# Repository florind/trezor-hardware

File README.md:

# Hardware design of Trezor

##
Using only 0603 components instead of 0402. Beware, the pushbuttons are also changed with https://www.mouser.de/ProductDetail/506-147873-2 (I have those).

https://trezor.io/

## Open Source Hardware

The content of this repo is dual licensed under the following licenses:
* [GNU Affero General Public License v3](COPYING)
* [CERN Open Hardware Licence Version 2 - Strongly Reciprocal](LICENSE)

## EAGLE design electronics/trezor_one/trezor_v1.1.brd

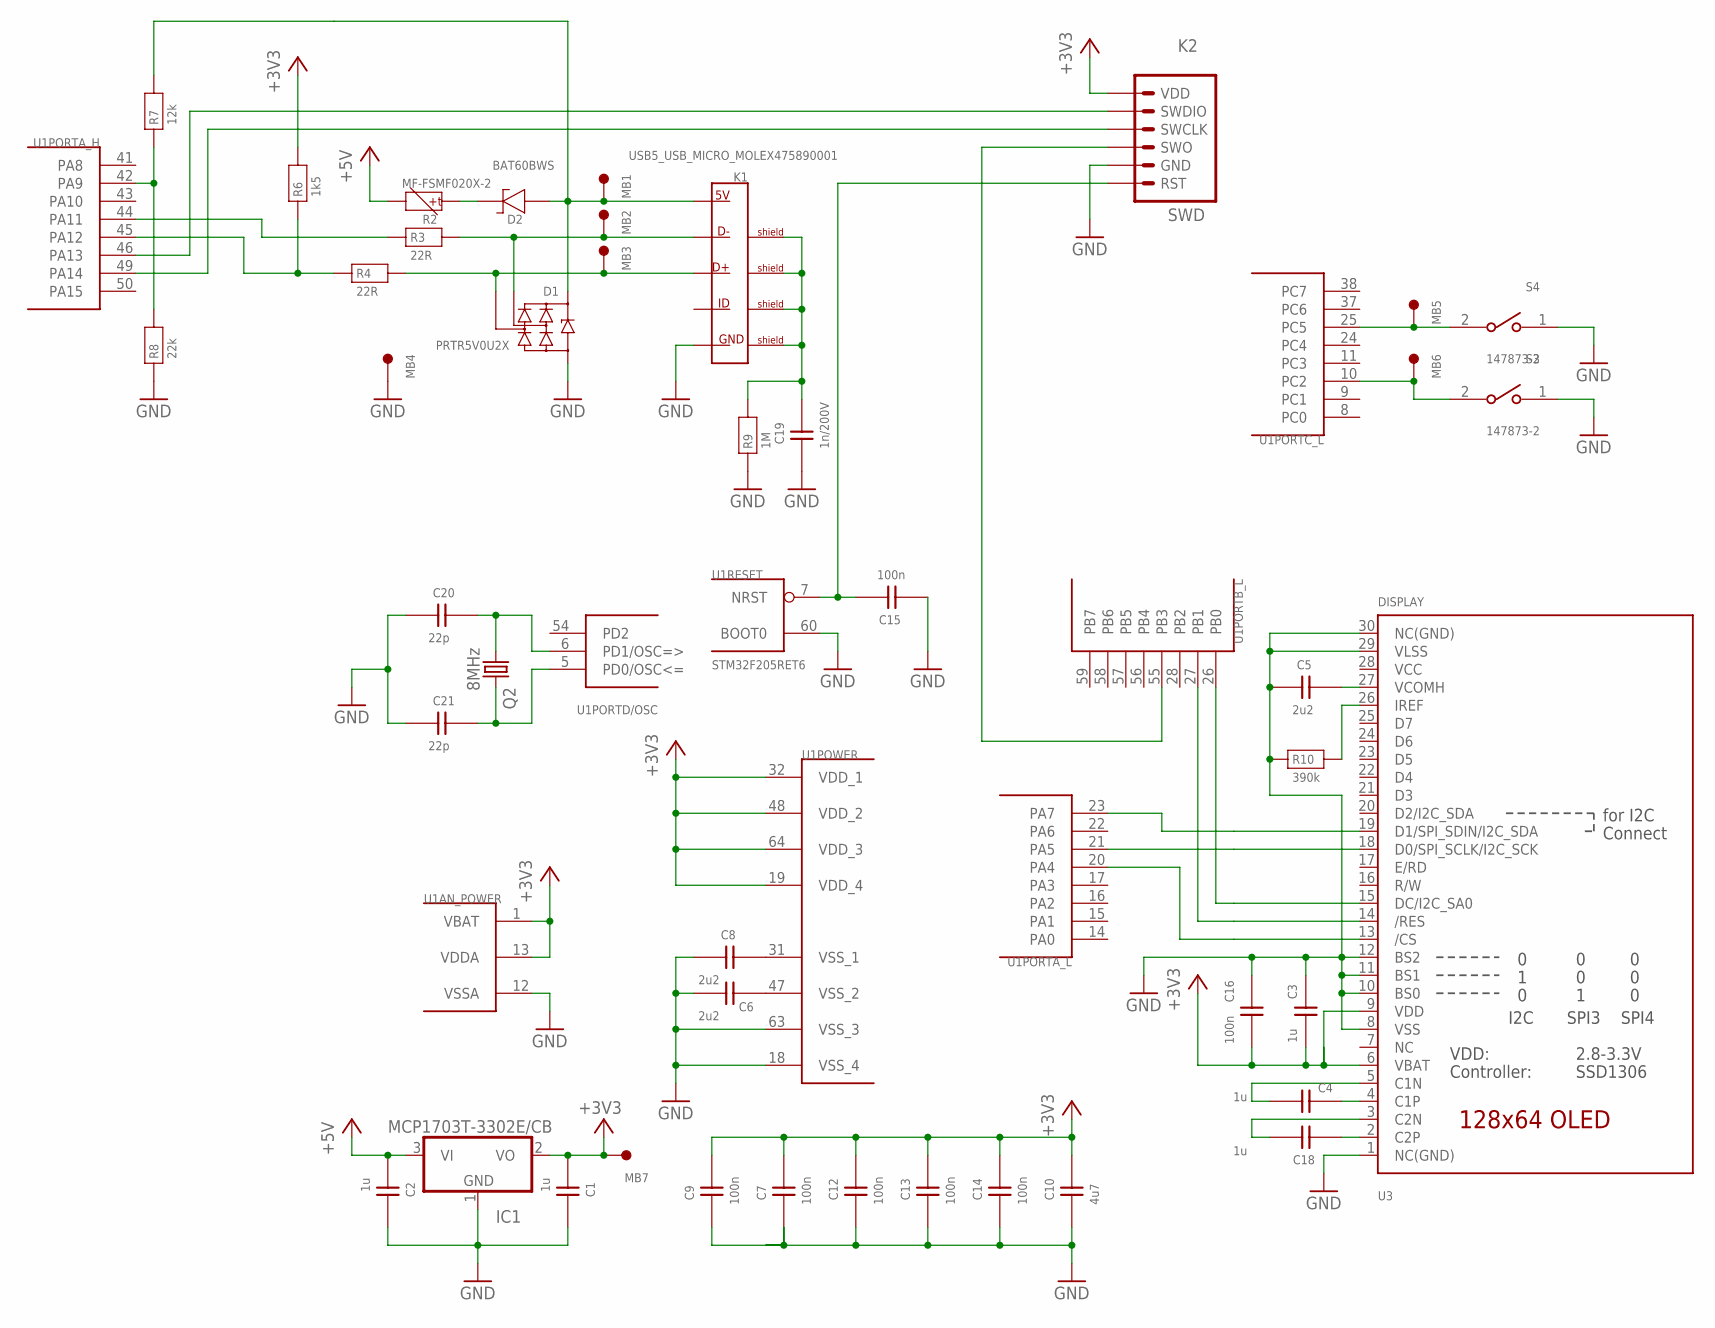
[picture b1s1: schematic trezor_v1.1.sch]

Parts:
C1, C2, C3, C4, C18: 1u; 0603
C5, C6, C8: 2u2; 0603
C7, C9, C12, C13, C14, C15, C16: 100n; 0603
C10: 4u7; 0603
C19: 1n/200V; 0603
C20, C21: 22p; 0603
D1: PRTR5V0U2X; SOT143B
D2: BAT60BWS; SOD323
IC1: MCP1703T-3302E/CB; SOT23
K1: USB5_USB_MICRO_MOLEX475890001; USB_MICRO-MOLEX475890001
K2: SWD
MB1, MB2, MB3, MB4, MB5, MB6, MB7: MB_1.50; MB1.5
Q2: 8MHz; CTS406
R2: MF-FSMF020X-2; 0603
R3, R4: 22R; 0603
R6: 1k5; 0603
R7: 12k; 0603
R8: 22k; 0603
R9: 1M; 0603
R10: 390k; 0603
S3, S4: 147873-2; SW_147873-2
U1: STM32F205RET6; TQFP64
U3: DISPLAY; UG-2864HSWEG01_0.96IN_WRAPAROUND

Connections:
+3V3: C1.1, C3.1, C7.2, C9.2, C10.2, C12.2, C13.2, C14.2, C16.1, IC1.2 (VO), K2.6 (VDD), MB7.1, R6.2, U1.1 (VBAT), U1.13 (VDDA), U1.19 (VDD_4), U1.32 (VDD_1), U1.48 (VDD_2), U1.64 (VDD_3), U3.6 (VBAT), U3.9 (VDD)
+5V: C2.1, IC1.3 (VI), R2.2
GND: C1.2, C2.2, C3.2, C5.1, C6.1, C7.1, C8.1, C9.1, C10.1, C12.1, C13.1, C14.1, C15.1, C16.2, C19.1, C20.1, C21.1, D1.1 (GND), IC1.1 (GND), K1.5 (5_GND), K2.2 (GND), MB4.1, R8.1, R9.1, R10.1, S3.1, S4.1, U1.12 (VSSA), U1.18 (VSS_4), U1.60 (BOOT0), U1.63 (VSS_3), U3.1 (NC(GND)), U3.8 (VSS), U3.10 (BS0), U3.11 (BS1), U3.12 (BS2), U3.29 (VLSS), U3.30 (NC(GND))
unnamed: U1.23 (PA7), U3.19 (D1/SPI_SDIN/I2C_SDA)
unnamed: C15.2, K2.1 (RST), U1.7 (NRST)
unnamed: U1.26 (PB0), U3.15 (DC/I2C_SA0)
unnamed: C8.2, U1.31 (VSS_1)
unnamed: U1.21 (PA5), U3.18 (D0/SPI_SCLK/I2C_SCK)
unnamed: C5.2, U3.27 (VCOMH)
unnamed: U1.27 (PB1), U3.14 (/RES)
unnamed: C6.2, U1.47 (VSS_2)
unnamed: R10.2, U3.26 (IREF)
unnamed: C18.1, U3.2 (C2P)
unnamed: C4.1, U3.4 (C1P)
unnamed: C18.2, U3.3 (C2N)
unnamed: C4.2, U3.5 (C1N)
unnamed: K2.3 (SWO), U1.55 (PB3)
unnamed: K2.5 (SWDIO), U1.46 (PA13)
unnamed: U1.20 (PA4), U3.13 (/CS)
unnamed: K2.4 (SWCLK), U1.49 (PA14)
unnamed: R3.1, U1.44 (PA11)
unnamed: MB5.1, S4.2, U1.25 (PC5)
unnamed: MB6.1, S3.2, U1.10 (PC2)
unnamed: D1.4 (VCC), D2.A (1), K1.1 (1_5V), MB1.1, R7.2
unnamed: D2.K (2), R2.1
unnamed: D1.2 (I/O1), K1.2 (2_D-), MB2.1, R3.2
unnamed: D1.3 (I/O2), K1.3 (3_D+), MB3.1, R4.2
unnamed: C19.2, K1.S1_BOT (SHIELD_1), K1.S1_TOP (SHIELD_1), K1.S2_BOT (SHIELD_2), K1.S2_TOP (SHIELD_2), K1.S3_BOT (SHIELD_3), K1.S3_TOP (SHIELD_3), K1.S4_BOT (SHIELD_4), K1.S4_TOP (SHIELD_4), K1.SA (SHIELD_1), K1.SB (SHIELD_2), R9.2
unnamed: R7.1, R8.2, U1.42 (PA9)
USB_D_P: R4.1, R6.1, U1.45 (PA12)
VCC: U3.28 (VCC)
XTAL1: C20.2, Q2.1, U1.6 (PD1/OSC=>)
XTAL2: C21.2, Q2.3 (2), U1.5 (PD0/OSC<=)

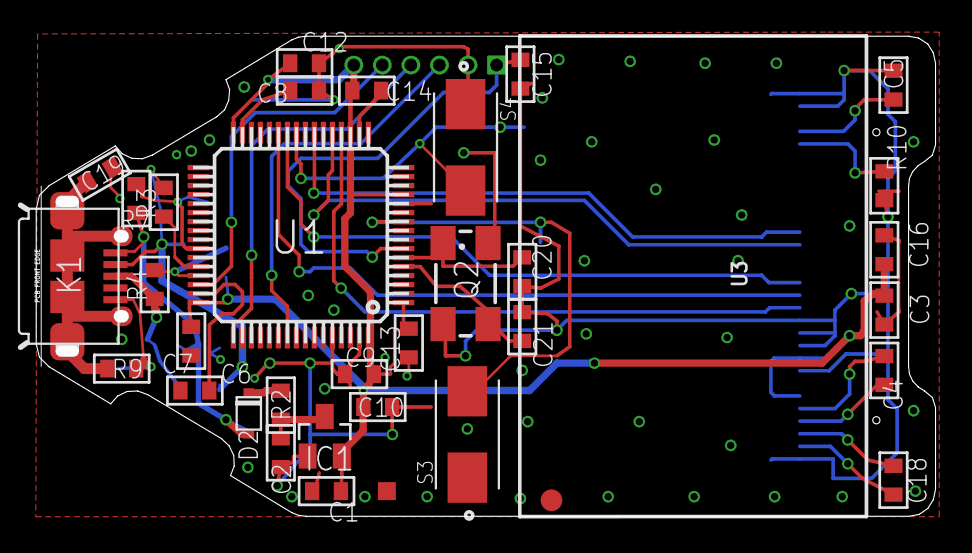
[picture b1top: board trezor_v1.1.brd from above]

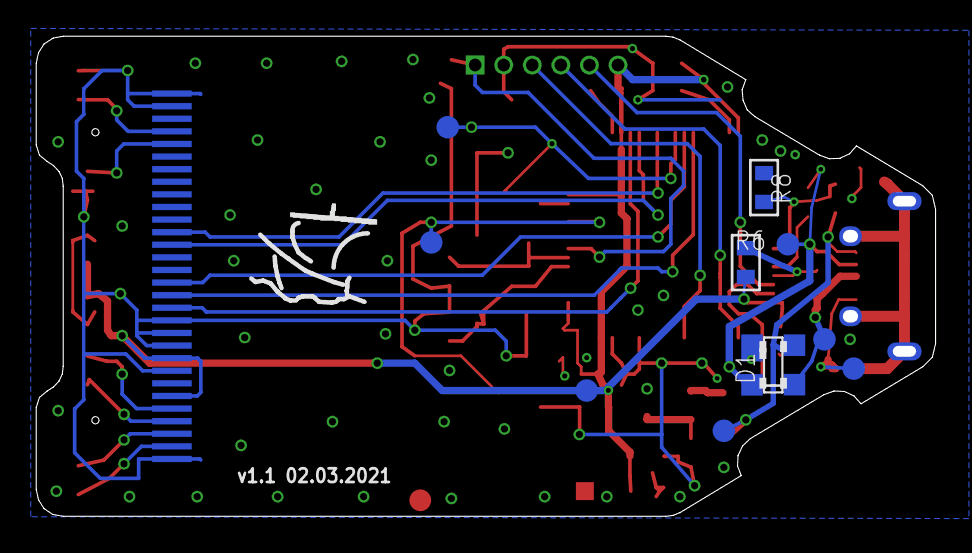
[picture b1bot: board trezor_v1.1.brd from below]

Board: 2 copper layers, 50.0 x 26.7 mm, 47 parts (10 on the bottom side), 32 nets.

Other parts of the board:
U$1: NEWSPLORE_LOGO_BPLACE_MID
U$3: BADMARK
U$4: CENTR

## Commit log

2021-03-02 Using 0603 passives, changed pushbutton

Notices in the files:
parts and their libraries:
microbuilder: This work is placed in the public domain, and may be freely used for commercial and non-commercial work with the following conditions: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
